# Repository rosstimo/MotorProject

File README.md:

# MotorProject
Super Fantastic Motor Project

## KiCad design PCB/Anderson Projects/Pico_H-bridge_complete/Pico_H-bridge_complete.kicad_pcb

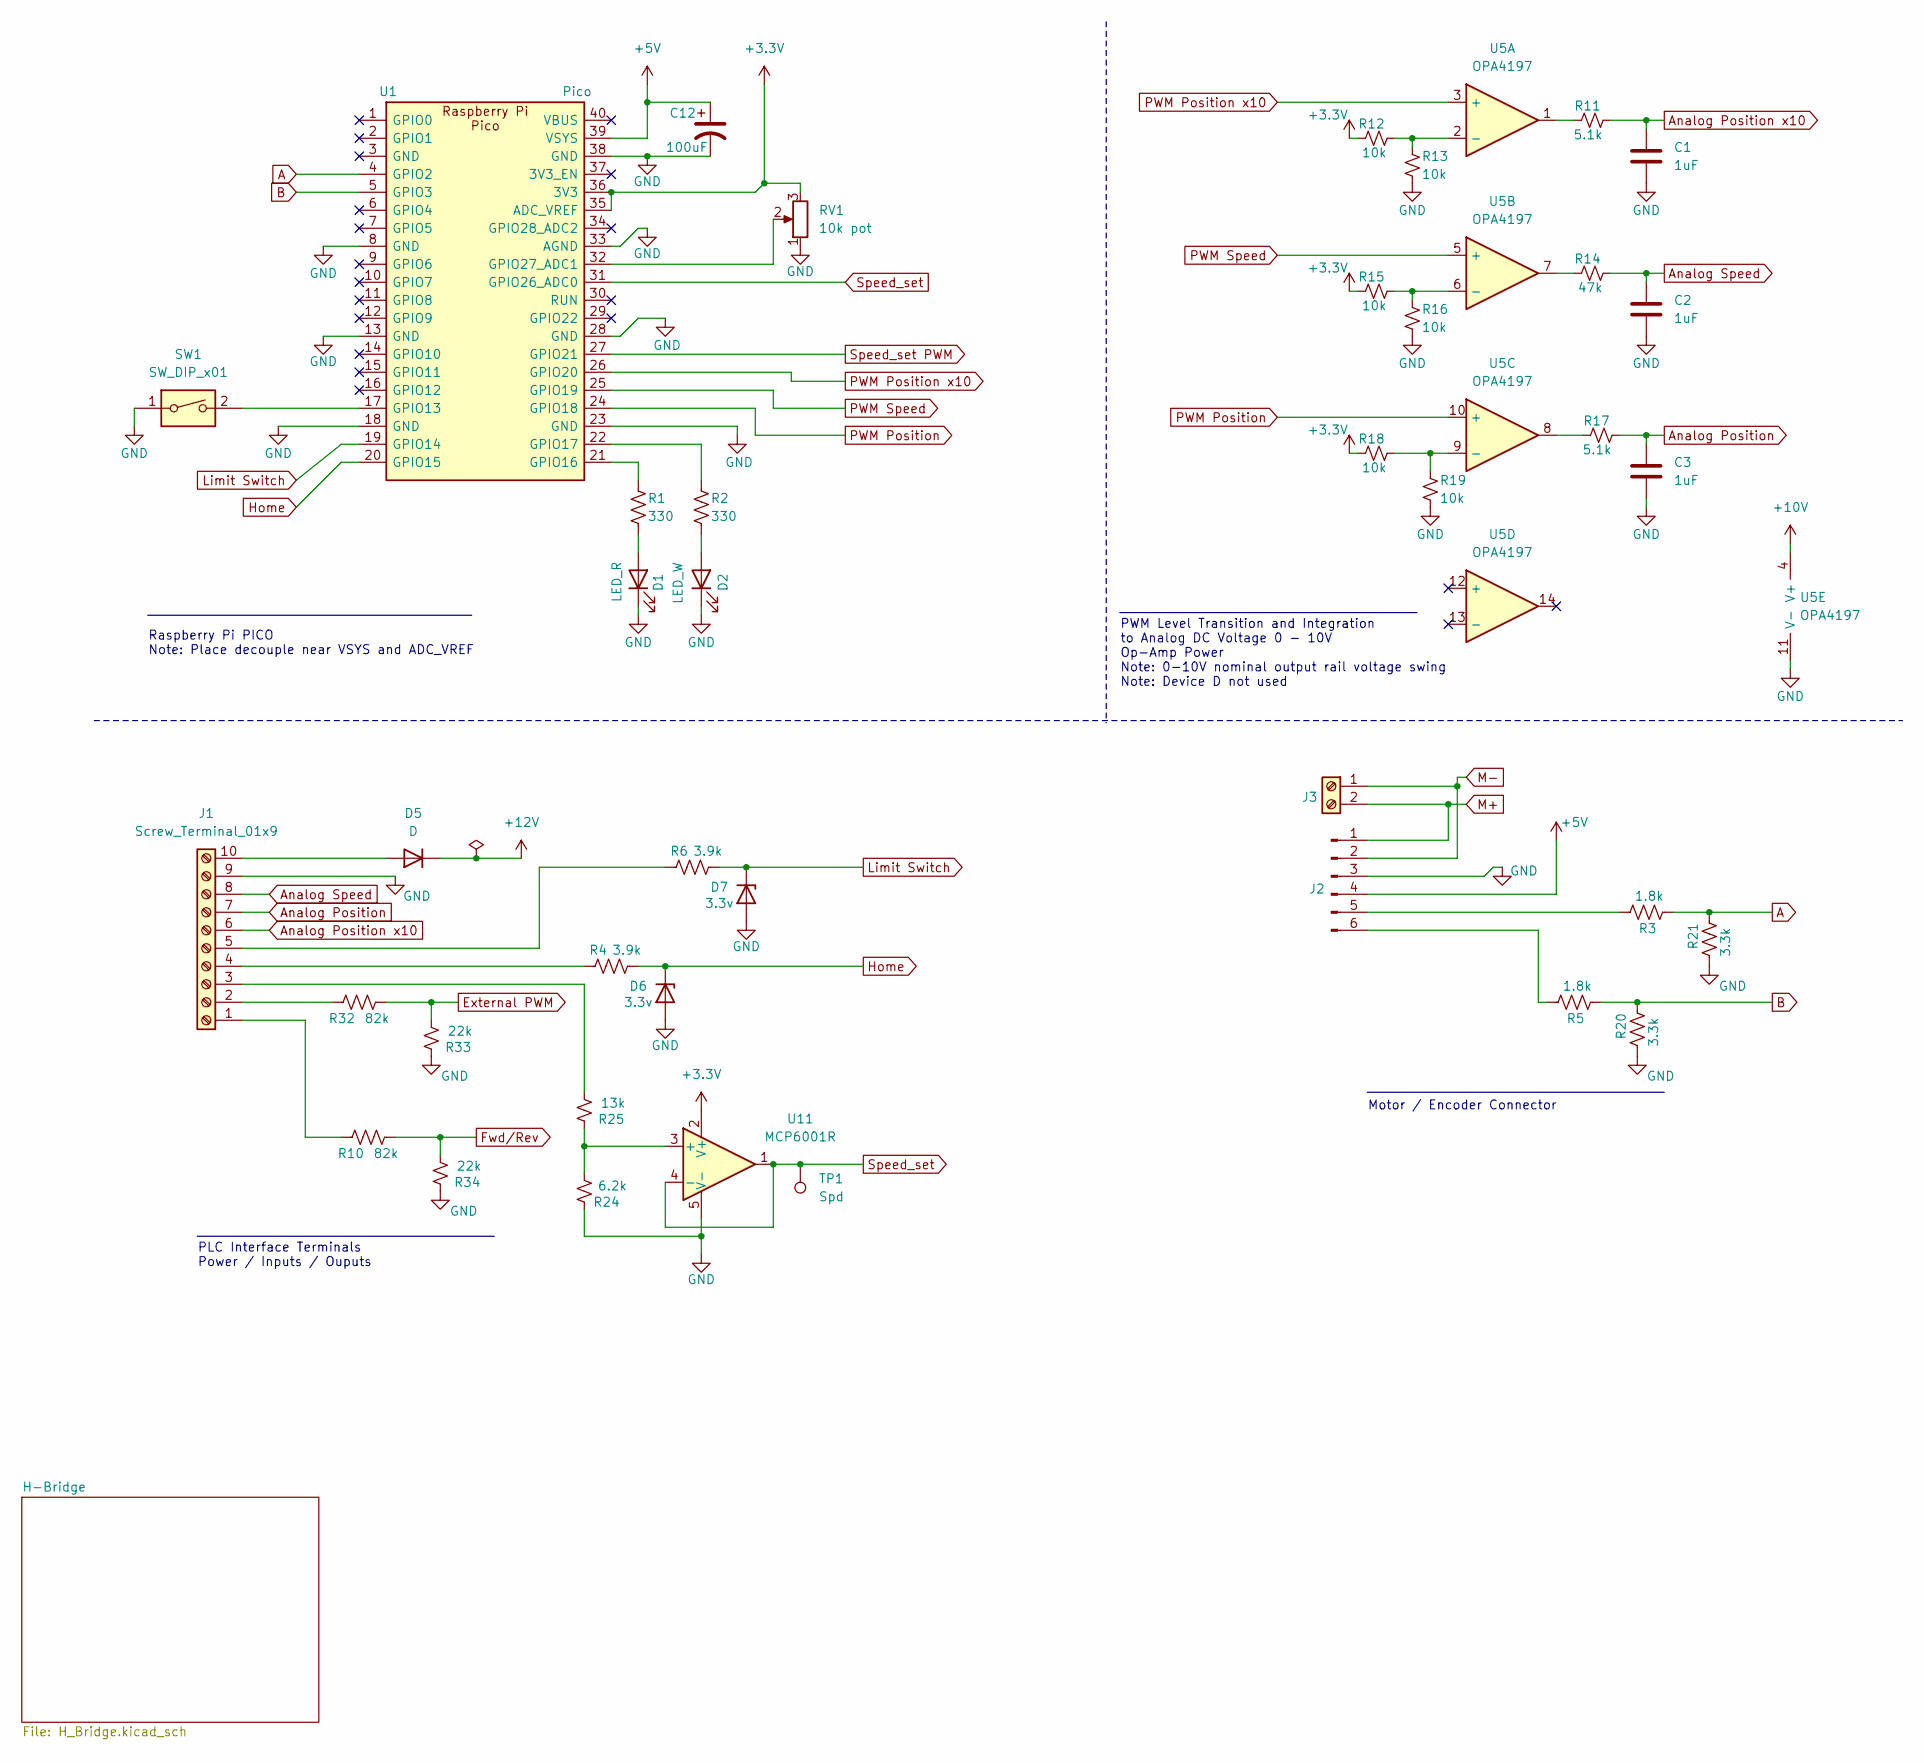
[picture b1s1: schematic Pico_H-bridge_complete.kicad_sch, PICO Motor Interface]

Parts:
C1, C2, C3: 1uF; C_1206_3216Metric; LCSC C2167419
C12: 100uF; C_1210_3225Metric; LCSC C23742
D1: LED_R; LED_0805_2012Metric; LCSC C84256
D2: LED_W; LED_0805_2012Metric; LCSC C34499
D5: D; D_SMA; LCSC C8678
D6, D7: 3.3v; D_SOD-323; LCSC C19077437
J1: Screw_Terminal_01x9; TerminalBlock_Phoenix_PT-1,5-10-5.0-H_1x10_P5.00mm_Horizont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
J2: Motor Connector; JST_XH_B6B-XH-A_1x06_P2.50mm_Vertical
J3: Screw_Terminal_01x02; TerminalBlock_Phoenix_MKDS-1,5-2_1x02_P5.00mm_Horizontal
R1, R2: 330; R_0805_2012Metric_Pad1.20x1.40mm_HandSolder; LCSC C17630
R3, R5: 1.8k; R_0805_2012Metric_Pad1.20x1.40mm_HandSolder; LCSC C17398
R4, R6: 3.9k; R_0805_2012Metric_Pad1.20x1.40mm_HandSolder; LCSC C17614
R10, R32: 82k; R_0805_2012Metric_Pad1.20x1.40mm_HandSolder; LCSC C17840
R11, R17: 5.1k; R_0805_2012Metric_Pad1.20x1.40mm_HandSolder; LCSC C27834
R12, R13, R15, R16, R18, R19: 10k; R_0805_2012Metric_Pad1.20x1.40mm_HandSolder; LCSC C17414
R14: 47k; R_0805_2012Metric_Pad1.20x1.40mm_HandSolder; LCSC C17713
R20, R21: 3.3k; R_0805_2012Metric_Pad1.20x1.40mm_HandSolder; LCSC C26010
R24: 6.2k; R_0805_2012Metric_Pad1.20x1.40mm_HandSolder; LCSC C17767
R25: 13k; R_0805_2012Metric_Pad1.20x1.40mm_HandSolder; LCSC C17455
R33, R34: 22k; R_0805_2012Metric_Pad1.20x1.40mm_HandSolder; LCSC C17560
RV1: 10k pot; Potentiometer_Bourns_3314J_Vertical; LCSC C36376
SW1: SW_DIP_x01; DIP_1x01_3.5_6.2mm; LCSC C600988
TP1: Spd; TestPoint_Plated_Hole_D2.0mm
U1: Pico; RaspberryPi_Pico
U5: OPA4197; SO-14_5.4_P1.27; LCSC C2058532
U11: MCP6001R; SOT-23-5; LCSC C154973

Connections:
+3.3V: R12.1, R15.1, R18.1, RV1.3, U1.35 (ADC_VREF), U1.36 (3V3), U11.2 (V+)
+5V: C12.1, J2.4, U1.39 (VSYS); also elsewhere on the board
+10V: U5.4 (V+); also elsewhere on the board
+12V: D5.1 (K); also elsewhere on the board
A: R3.2, R21.1, U1.4 (GPIO2)
Analog Position: C3.1, J1.7, R17.2
Analog Position x10: C1.1, J1.6, R11.2
Analog Speed: C2.1, J1.8, R14.2
B: R5.2, R20.1, U1.5 (GPIO3)
External PWM: R32.2, R33.2; also elsewhere on the board
Fwd/Rev: R10.2, R34.2; also elsewhere on the board
GND: C1.2, C2.2, C3.2, C12.2, D1.1 (K), D2.1 (K), D6.2 (A), D7.2 (A), J1.9, J2.3, R13.2, R16.2, R19.2, R20.2, R21.2, R24.1, R33.1, R34.1, RV1.1, SW1.1, U1.8 (GND), U1.13 (GND), U1.18 (GND), U1.23 (GND), U1.28 (GND), U1.33 (AGND), U1.38 (GND), U5.11 (V-), U11.5 (V-); also elsewhere on the board
Home: D6.1 (K), R4.2, U1.20 (GPIO15)
Limit Switch: D7.1 (K), R6.2, U1.19 (GPIO14)
M+: J2.1, J3.2; also elsewhere on the board
M-: J2.2, J3.1; also elsewhere on the board
unnamed: D1.2 (A), R1.2
unnamed: D2.2 (A), R2.2
unnamed: D5.2 (A), J1.10
unnamed: J1.1, R10.1
unnamed: J1.2, R32.1
unnamed: J1.3, R25.2
unnamed: J1.4, R4.1
unnamed: J1.5, R6.1
unnamed: J2.5, R3.1
unnamed: J2.6, R5.1
unnamed: R11.1, U5.1
unnamed: R14.1, U5.7
unnamed: R17.1, U5.8
unnamed: SW1.2, U1.17 (GPIO13)
unnamed: R1.1, U1.21 (GPIO16)
unnamed: R2.1, U1.22 (GPIO17)
unnamed: RV1.2, U1.32 (GPIO27_ADC1)
unnamed: R12.2, R13.1, U5.2 (-)
unnamed: R15.2, R16.1, U5.6 (-)
unnamed: R18.2, R19.1, U5.9 (-)
unnamed: R24.2, R25.1, U11.3 (+)
PWM Position: U1.24 (GPIO18), U5.10 (+)
PWM Position x10: U1.26 (GPIO20), U5.3 (+)
PWM Speed: U1.25 (GPIO19), U5.5 (+)
Speed_set: TP1.1, U1.31 (GPIO26_ADC0), U11.1, U11.4 (-)
Speed_set PWM: U1.27 (GPIO21); also elsewhere on the board

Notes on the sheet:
PWM Level Transition and Integration to Analog DC Voltage 0 - 10V Op-Amp Power Note: 0-10V nominal output rail voltage swing Note: Device D not used
PLC Interface Terminals Power / Inputs / Ouputs
Motor / Encoder Connector
Raspberry Pi PICO Note: Place decouple near VSYS and ADC_VREF

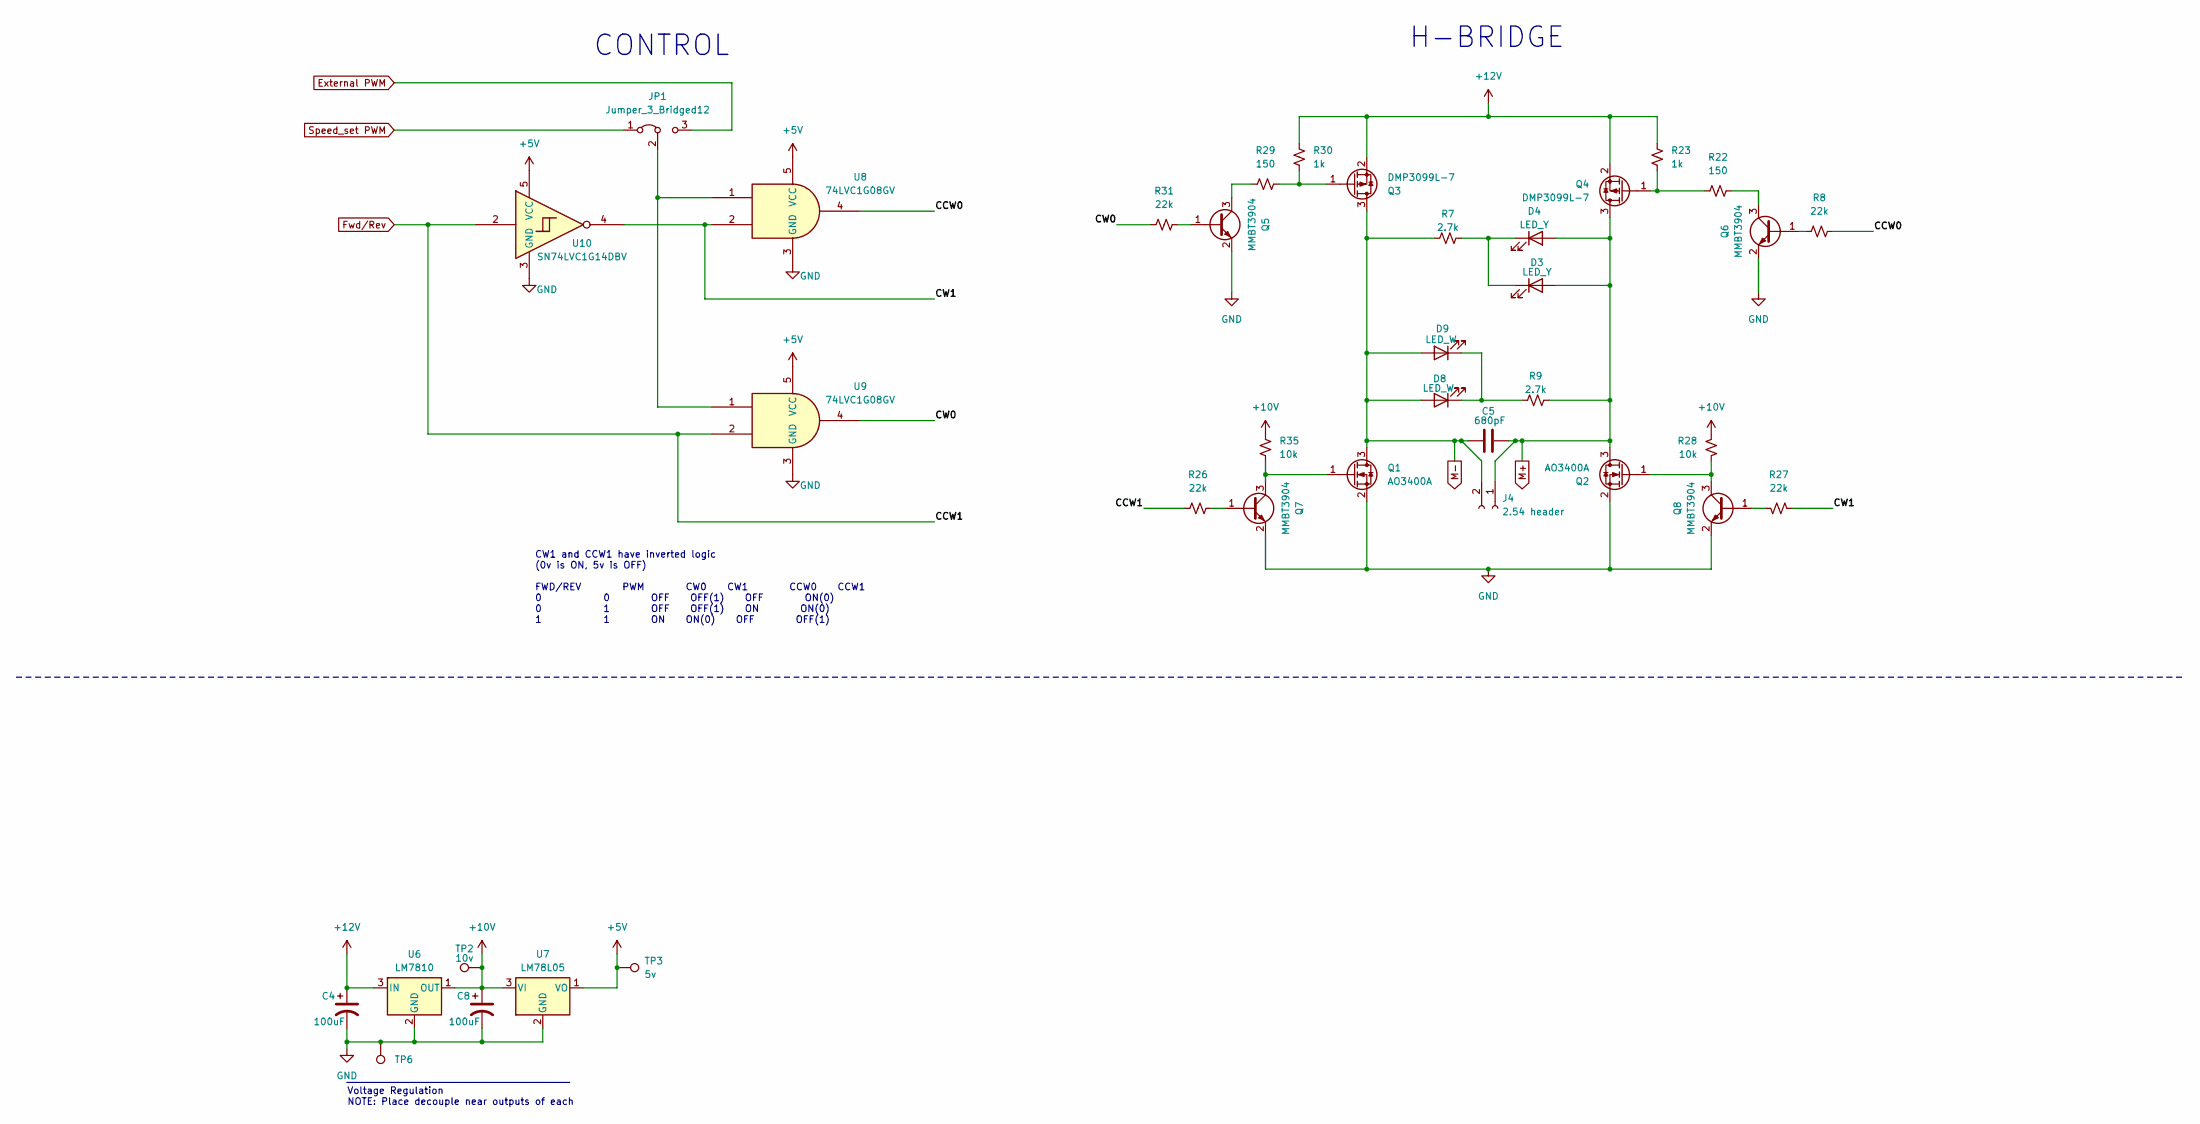
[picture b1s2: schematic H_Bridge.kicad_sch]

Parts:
C4, C8: 100uF; C_1210_3225Metric; LCSC C23742
C5: 680pF; C_0603_1608Metric; LCSC C1630
D3, D4: LED_Y; LED_0603_1608Metric; LCSC C2286
D8, D9: LED_W; LED_0603_1608Metric; LCSC C2290
J4: 2.54 header; PinHeader_1x02_P2.54mm_Vertical
JP1: Jumper_3_Bridged12; PinHeader_1x03_P2.54mm_Vertical
Q1, Q2: AO3400A; SOT-23; LCSC C20917
Q3, Q4: DMP3099L-7; SOT-23; LCSC C155244
Q5, Q6, Q7, Q8: MMBT3904; SOT-23; LCSC C20526
R7, R9: 2.7k; R_0805_2012Metric_Pad1.20x1.40mm_HandSolder; LCSC C17530
R8, R26, R27, R31: 22k; R_0805_2012Metric_Pad1.20x1.40mm_HandSolder; LCSC C17560
R22, R29: 150; R_0805_2012Metric_Pad1.20x1.40mm_HandSolder; LCSC C17471
R23, R30: 1k; R_0805_2012Metric_Pad1.20x1.40mm_HandSolder; LCSC C17513
R28, R35: 10k; R_0805_2012Metric_Pad1.20x1.40mm_HandSolder; LCSC C17414
TP2: 10v; TestPoint_Plated_Hole_D2.0mm
TP3: 5v; TestPoint_Plated_Hole_D2.0mm
TP6: GND; TestPoint_Loop_D2.60mm_Drill1.4mm_Beaded
U6: LM7810; SOT-89-3; LCSC C122848
U7: LM78L05; SOT-89-3; LCSC C347258
U8, U9: 74LVC1G08GV; SOT-23-5; LCSC C19829591
U10: SN74LVC1G14DBV; SOT-23-5; LCSC C7835

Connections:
+5V: TP3.1, U7.1 (VO), U8.5 (VCC), U9.5 (VCC), U10.5 (VCC); also elsewhere on the board
+10V: C8.1, R28.1, R35.1, TP2.1, U6.1 (OUT), U7.3 (VI); also elsewhere on the board
+12V: C4.1, Q3.2 (S), Q4.2 (S), R23.2, R30.2, U6.3 (IN); also elsewhere on the board
/H-Bridge/CCW0: R8.2, U8.4
/H-Bridge/CW0: R31.1, U9.4
/H-Bridge/CW1: R27.1, U8.2, U10.4
External PWM: JP1.3 (B); also elsewhere on the board
Fwd/Rev: R26.1, U9.2, U10.2; also elsewhere on the board
GND: C4.2, C8.2, Q1.2 (S), Q2.2 (S), Q5.2 (E), Q6.2 (E), Q7.2 (E), Q8.2 (E), TP6.1, U6.2 (GND), U7.2 (GND), U8.3 (GND), U9.3 (GND), U10.3 (GND); also elsewhere on the board
M+: C5.2, D3.2 (A), D4.2 (A), J4.1, Q2.3 (D), Q4.3 (D), R9.1; also elsewhere on the board
M-: C5.1, D8.2 (A), D9.2 (A), J4.2, Q1.3 (D), Q3.3 (D), R7.2; also elsewhere on the board
unnamed: D3.1 (K), D4.1 (K), R7.1
unnamed: D8.1 (K), D9.1 (K), R9.2
unnamed: JP1.2 (C), U8.1, U9.1
unnamed: Q1.1 (G), Q7.3 (C), R35.2
unnamed: Q2.1 (G), Q8.3 (C), R28.2
unnamed: Q3.1 (G), R29.2, R30.1
unnamed: Q4.1 (G), R22.1, R23.1
unnamed: Q5.1 (B), R31.2
unnamed: Q5.3 (C), R29.1
unnamed: Q6.1 (B), R8.1
unnamed: Q6.3 (C), R22.2
unnamed: Q7.1 (B), R26.2
unnamed: Q8.1 (B), R27.2
Speed_set PWM: JP1.1 (A); also elsewhere on the board

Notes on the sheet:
Voltage Regulation NOTE: Place decouple near outputs of each
CONTROL
CW1 and CCW1 have inverted logic (0v is ON, 5v is OFF) FWD/REV PWM CW0 CW1 CCW0 CCW1 0 0 OFF OFF(1) OFF ON(0) 0 1 OFF OFF(1) ON ON(0) 1 1 ON ON(0) OFF OFF(1)
H-BRIDGE

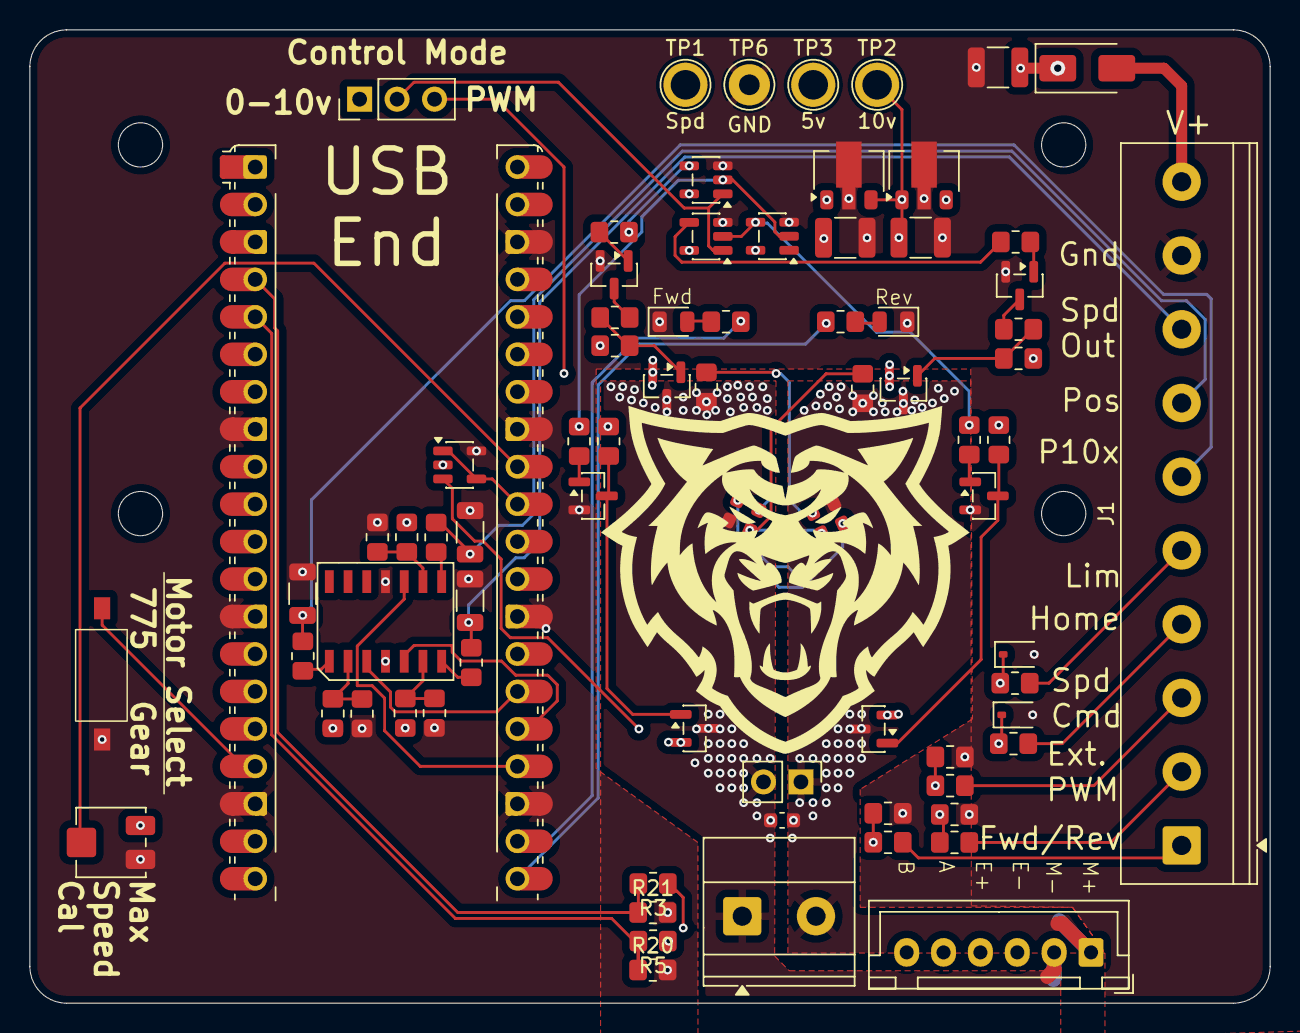
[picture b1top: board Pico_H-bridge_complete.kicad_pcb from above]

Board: 4 copper layers, 84.1 x 66.0 mm, 79 parts (0 on the bottom side), 58 nets.

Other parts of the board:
logo1: LOGO; Bengal_25_25(negative)

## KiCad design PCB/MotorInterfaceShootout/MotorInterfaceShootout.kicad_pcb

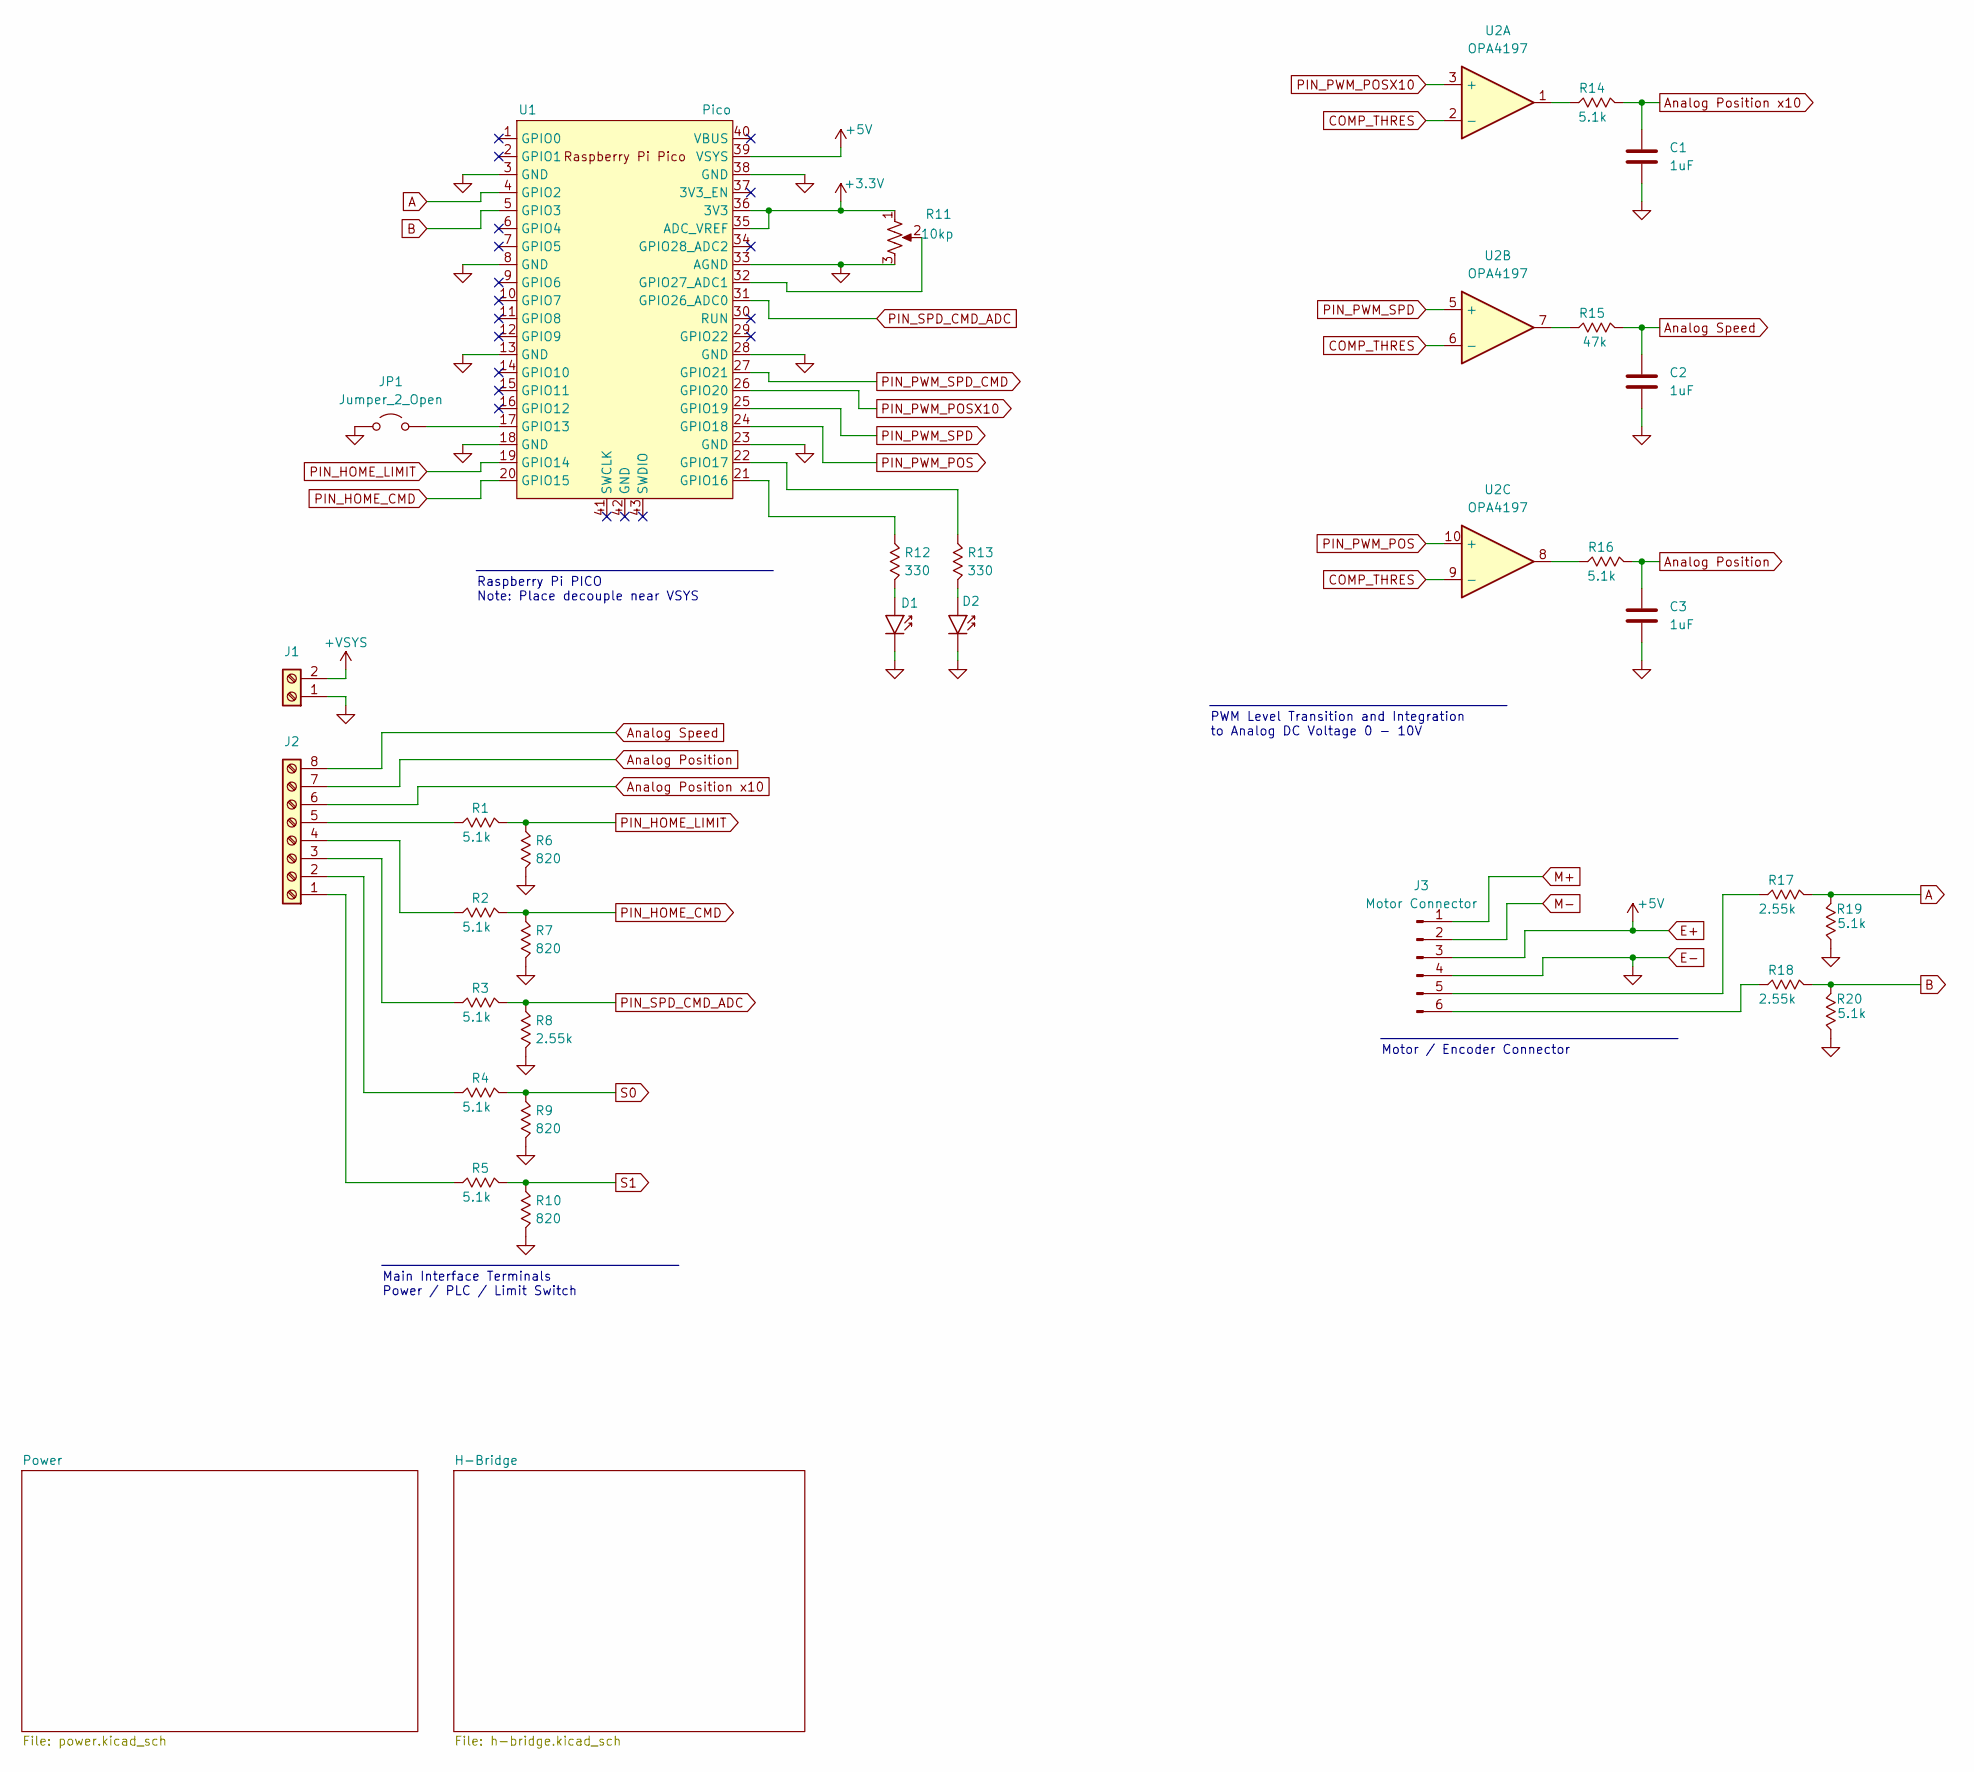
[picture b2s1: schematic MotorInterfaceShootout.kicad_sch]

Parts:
C1, C2, C3: 1uF; C_Rect_L7.3mm_W4.5_H9.5mm_P5.0mmx
D1: Red; LED_0805_2012Metric_Pad1.15x1.40mm_HandSolder
D2: Green; LED_0805_2012Metric_Pad1.15x1.40mm_HandSolder
J1: Screw_Terminal_01x02; TerminalBlock_WAGO_236-102_1x02_P5.00mm_45Degree
J2: Screw_Terminal_01x08; TerminalBlock_WAGO_236-108_1x08_P5.00mm_45Degree
J3: Motor Connector; JST_XH_B6B-XH-A_1x06_P2.50mm_Vertical
JP1: Jumper_2_Open; PinHeader_1x02_P2.54mm_Vertical
R1, R2, R3, R4, R5, R14, R16, R19, R20: 5.1k; R_0805_2012Metric
R6, R7, R9, R10: 820; R_0805_2012Metric
R8, R17, R18: 2.55k; R_0805_2012Metric
R11: 10kp; SOT_10KLFTR_BIT
R12, R13: 330; R_0805_2012Metric
R15: 47k; R_0805_2012Metric
U1: Pico; RPi_Pico_SMD_TH
U2: OPA4197; D14_TEX

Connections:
+3.3V: R11.1, U1.35 (ADC_VREF), U1.36 (3V3)
+VSYS: J1.2; also elsewhere on the board
A: R17.2, R19.2, U1.4 (GPIO2)
Analog Position: C3.1, J2.7, R16.2
Analog Position x10: C1.1, J2.6, R14.2
Analog Speed: C2.1, J2.8, R15.2
B: R18.2, R20.2, U1.5 (GPIO3)
COMP_THRES: U2.2 (-), U2.6 (-), U2.9 (-); also elsewhere on the board
E+: J3.3, U1.39 (VSYS); also elsewhere on the board
E-: C1.2, C2.2, C3.2, D1.1 (K), D2.1 (K), J1.1, J3.4, JP1.1 (A), R6.2, R7.2, R8.2, R9.2, R10.2, R11.3, R19.1, R20.1, U1.3 (GND), U1.8 (GND), U1.13 (GND), U1.18 (GND), U1.23 (GND), U1.28 (GND), U1.33 (AGND), U1.38 (GND); also elsewhere on the board
M+: J3.1; also elsewhere on the board
M-: J3.2; also elsewhere on the board
unnamed: D1.2 (A), R12.2
unnamed: D2.2 (A), R13.2
unnamed: J2.1, R5.1
unnamed: J2.2, R4.1
unnamed: J2.3, R3.1
unnamed: J2.4, R2.1
unnamed: J2.5, R1.1
unnamed: J3.5, R17.1
unnamed: J3.6, R18.1
unnamed: JP1.2 (B), U1.17 (GPIO13)
unnamed: R14.1, U2.1
unnamed: R15.1, U2.7
unnamed: R16.1, U2.8
unnamed: R12.1, U1.21 (GPIO16)
unnamed: R13.1, U1.22 (GPIO17)
unnamed: R11.2, U1.32 (GPIO27_ADC1)
PIN_HOME_CMD: R2.2, R7.1, U1.20 (GPIO15)
PIN_HOME_LIMIT: R1.2, R6.1, U1.19 (GPIO14)
PIN_PWM_POS: U1.24 (GPIO18), U2.10 (+)
PIN_PWM_POSX10: U1.26 (GPIO20), U2.3 (+)
PIN_PWM_SPD: U1.25 (GPIO19), U2.5 (+)
PIN_PWM_SPD_CMD: U1.27 (GPIO21); also elsewhere on the board
PIN_SPD_CMD_ADC: R3.2, R8.1, U1.31 (GPIO26_ADC0)
S0: R4.2, R9.1; also elsewhere on the board
S1: R5.2, R10.1; also elsewhere on the board

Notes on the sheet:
Motor / Encoder Connector
Raspberry Pi PICO Note: Place decouple near VSYS
PWM Level Transition and Integration to Analog DC Voltage 0 - 10V
Main Interface Terminals Power / PLC / Limit Switch

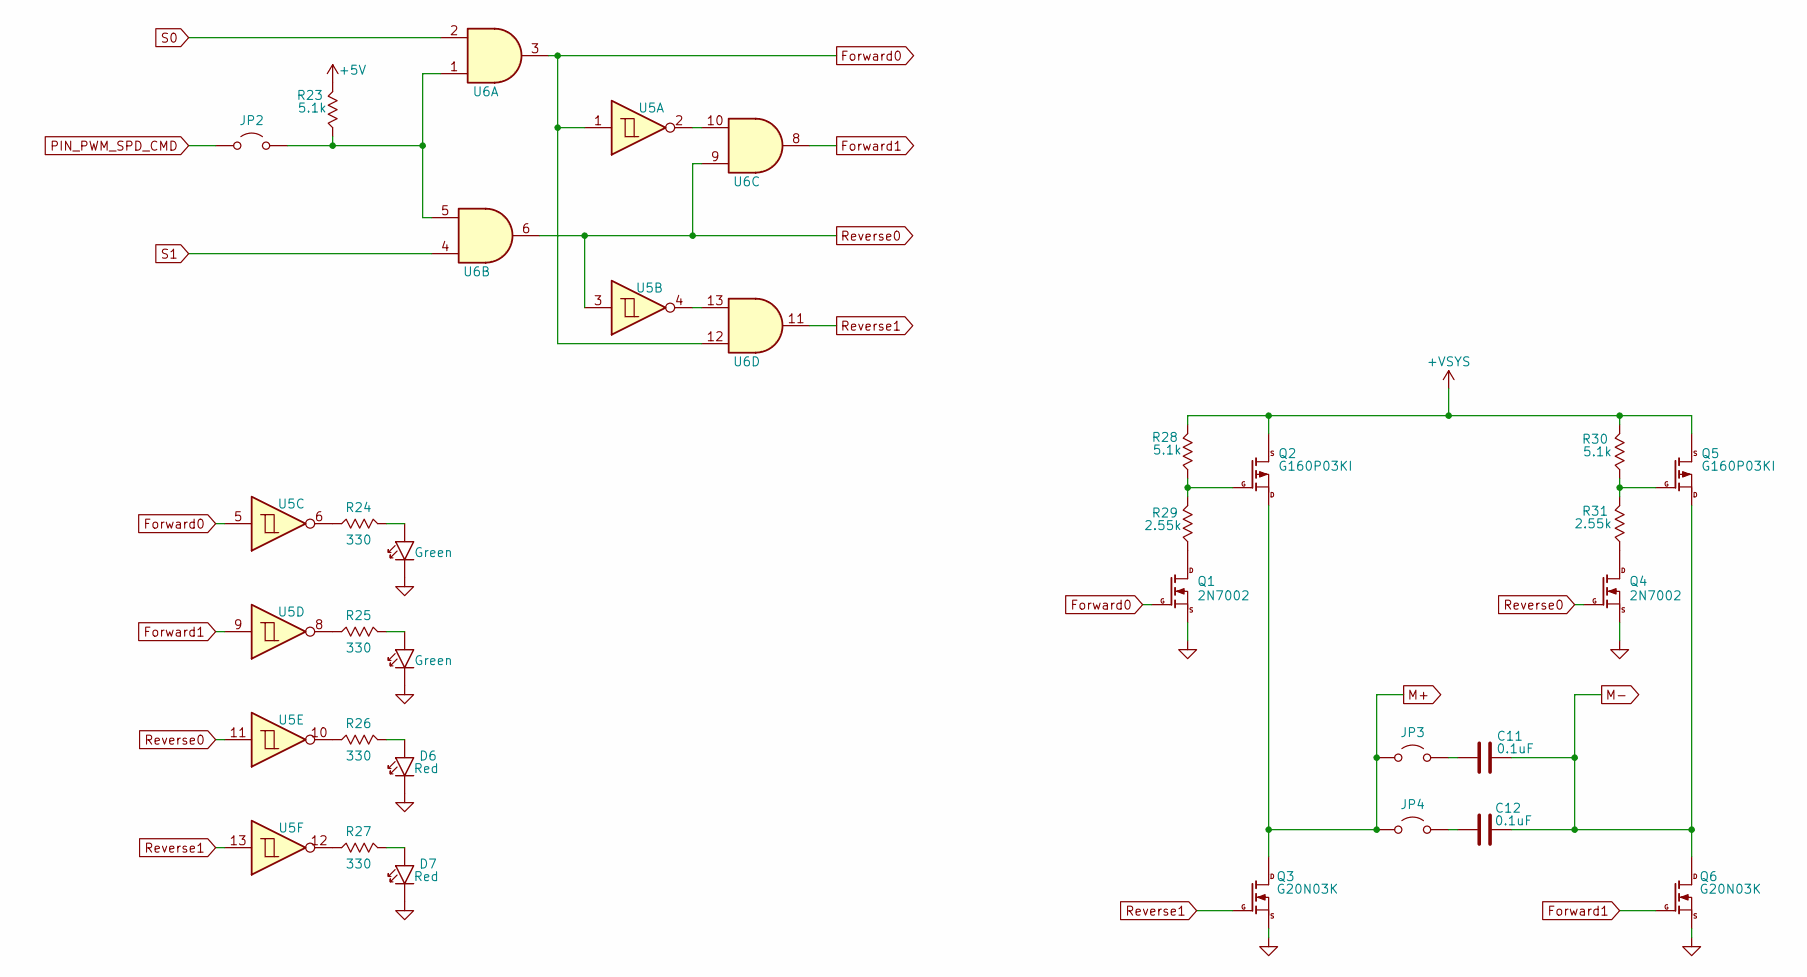
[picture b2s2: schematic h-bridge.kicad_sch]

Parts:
C11, C12: 0.1uF; C_0805_2012Metric
D4, D5: Green; LED_0805_2012Metric_Pad1.15x1.40mm_HandSolder
D6, D7: Red; LED_0805_2012Metric_Pad1.15x1.40mm_HandSolder
JP2, JP3, JP4: Jumper_2_Open; PinHeader_1x02_P2.54mm_Vertical
Q1, Q4: 2N7002; SOT-23
Q2, Q5: G160P03KI; TO-252-2
Q3, Q6: G20N03K; TO-252-2
R23, R28, R30: 5.1k; R_0805_2012Metric
R24, R25, R26, R27: 330; R_0805_2012Metric
R29, R31: 2.55k; R_0805_2012Metric
U5: 74LS14; SOIC-14_3.9x8.7mm_P1.27mm-D14-L
U6: 74LS08; SOIC-14_3.9x8.7mm_P1.27mm-D14-L

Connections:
+VSYS: Q2.3 (S), Q5.3 (S), R28.2, R30.2; also elsewhere on the board
E+: R23.2; also elsewhere on the board
E-: D4.1 (K), D5.1 (K), D6.1 (K), D7.1 (K), Q1.2 (S), Q3.3 (S), Q4.2 (S), Q6.3 (S); also elsewhere on the board
Forward0: Q1.1 (G), U5.1, U5.5, U6.3, U6.12
Forward1: Q6.1 (G), U5.9, U6.8
M+: JP3.1 (A), JP4.1 (A), Q2.2 (D), Q3.2 (D); also elsewhere on the board
M-: C11.2, C12.2, Q5.2 (D), Q6.2 (D); also elsewhere on the board
unnamed: D4.2 (A), R24.2
unnamed: D5.2 (A), R25.2
unnamed: D6.2 (A), R26.2
unnamed: D7.2 (A), R27.2
unnamed: JP2.2 (B), R23.1, U6.1, U6.5
unnamed: C11.1, JP3.2 (B)
unnamed: C12.1, JP4.2 (B)
unnamed: Q1.3 (D), R29.1
unnamed: Q2.1 (G), R28.1, R29.2
unnamed: Q4.3 (D), R31.1
unnamed: Q5.1 (G), R30.1, R31.2
unnamed: R24.1, U5.6
unnamed: R25.1, U5.8
unnamed: R26.1, U5.10
unnamed: R27.1, U5.12
unnamed: U5.2, U6.10
unnamed: U5.4, U6.13
PIN_PWM_SPD_CMD: JP2.1 (A); also elsewhere on the board
Reverse0: Q4.1 (G), U5.3, U5.11, U6.6, U6.9
Reverse1: Q3.1 (G), U5.13, U6.11
S0: U6.2; also elsewhere on the board
S1: U6.4; also elsewhere on the board

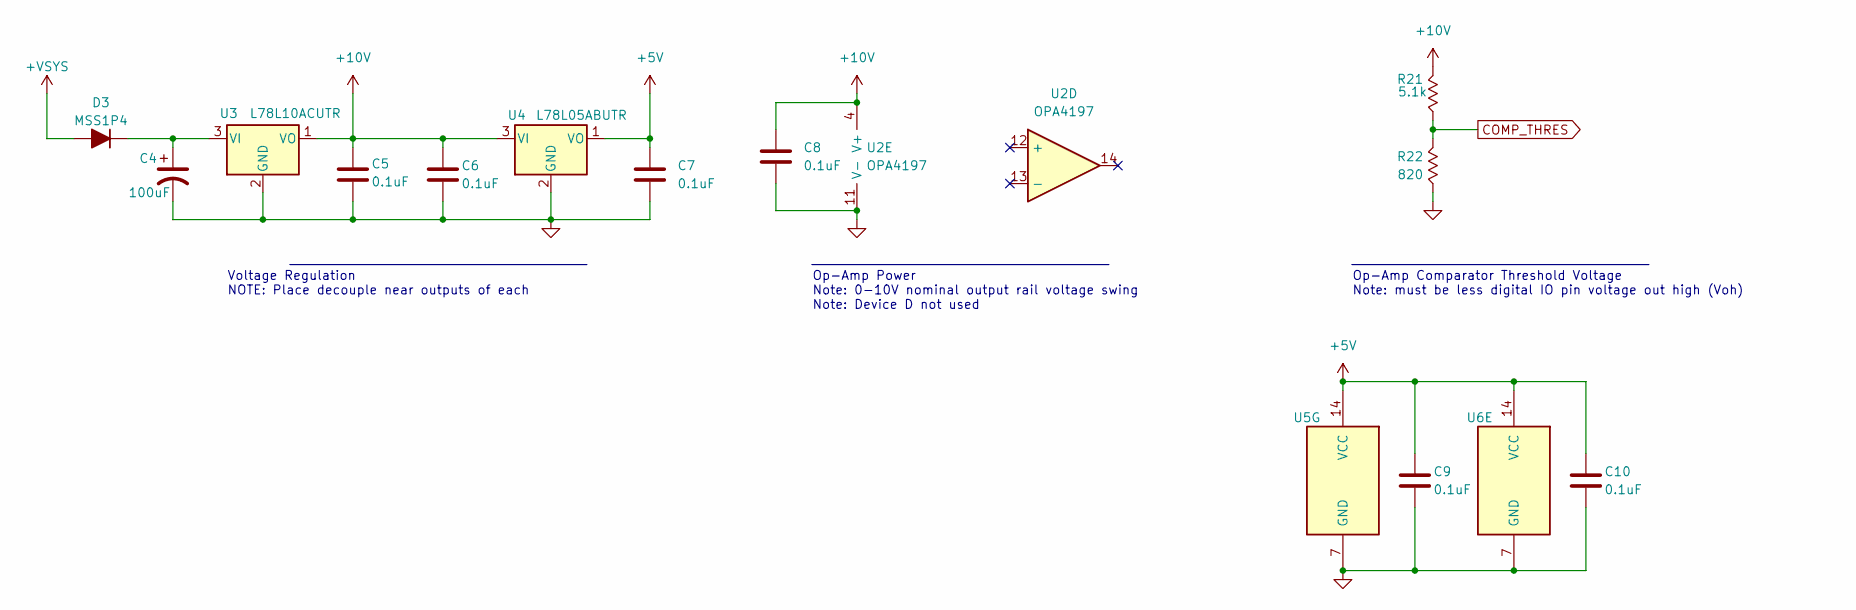
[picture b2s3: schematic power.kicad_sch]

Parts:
C4: 100uF; CP_Elec_6.3x7.7
C5, C6, C7, C8, C9, C10: 0.1uF; C_0805_2012Metric
D3: MSS1P4; D_MicroSMP_AK
R21: 5.1k; R_0805_2012Metric
R22: 820; R_0805_2012Metric
U2: OPA4197; D14_TEX
U3: L78L10ACUTR; SOT-89-3
U4: L78L05ABUTR; SOT-89-3
U5: 74LS14; SOIC-14_3.9x8.7mm_P1.27mm-D14-L
U6: 74LS08; SOIC-14_3.9x8.7mm_P1.27mm-D14-L

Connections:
+10V: C5.1, C6.1, C8.1, R21.2, U2.4 (V+), U3.1 (VO), U4.3 (VI)
+VSYS: D3.2 (A); also elsewhere on the board
COMP_THRES: R21.1, R22.1; also elsewhere on the board
E+: C7.1, C9.1, C10.1, U4.1 (VO), U5.14 (VCC), U6.14 (VCC); also elsewhere on the board
E-: C4.2, C5.2, C6.2, C7.2, C8.2, C9.2, C10.2, R22.2, U2.11 (V-), U3.2 (GND), U4.2 (GND), U5.7 (GND), U6.7 (GND); also elsewhere on the board
unnamed: C4.1, D3.1 (K), U3.3 (VI)

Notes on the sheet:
Voltage Regulation NOTE: Place decouple near outputs of each
Op-Amp Power Note: 0-10V nominal output rail voltage swing Note: Device D not used
Op-Amp Comparator Threshold Voltage Note: must be less digital IO pin voltage out high (Voh)

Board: 4 copper layers, 69 parts (23 on the bottom side), 60 nets, no tracks yet.

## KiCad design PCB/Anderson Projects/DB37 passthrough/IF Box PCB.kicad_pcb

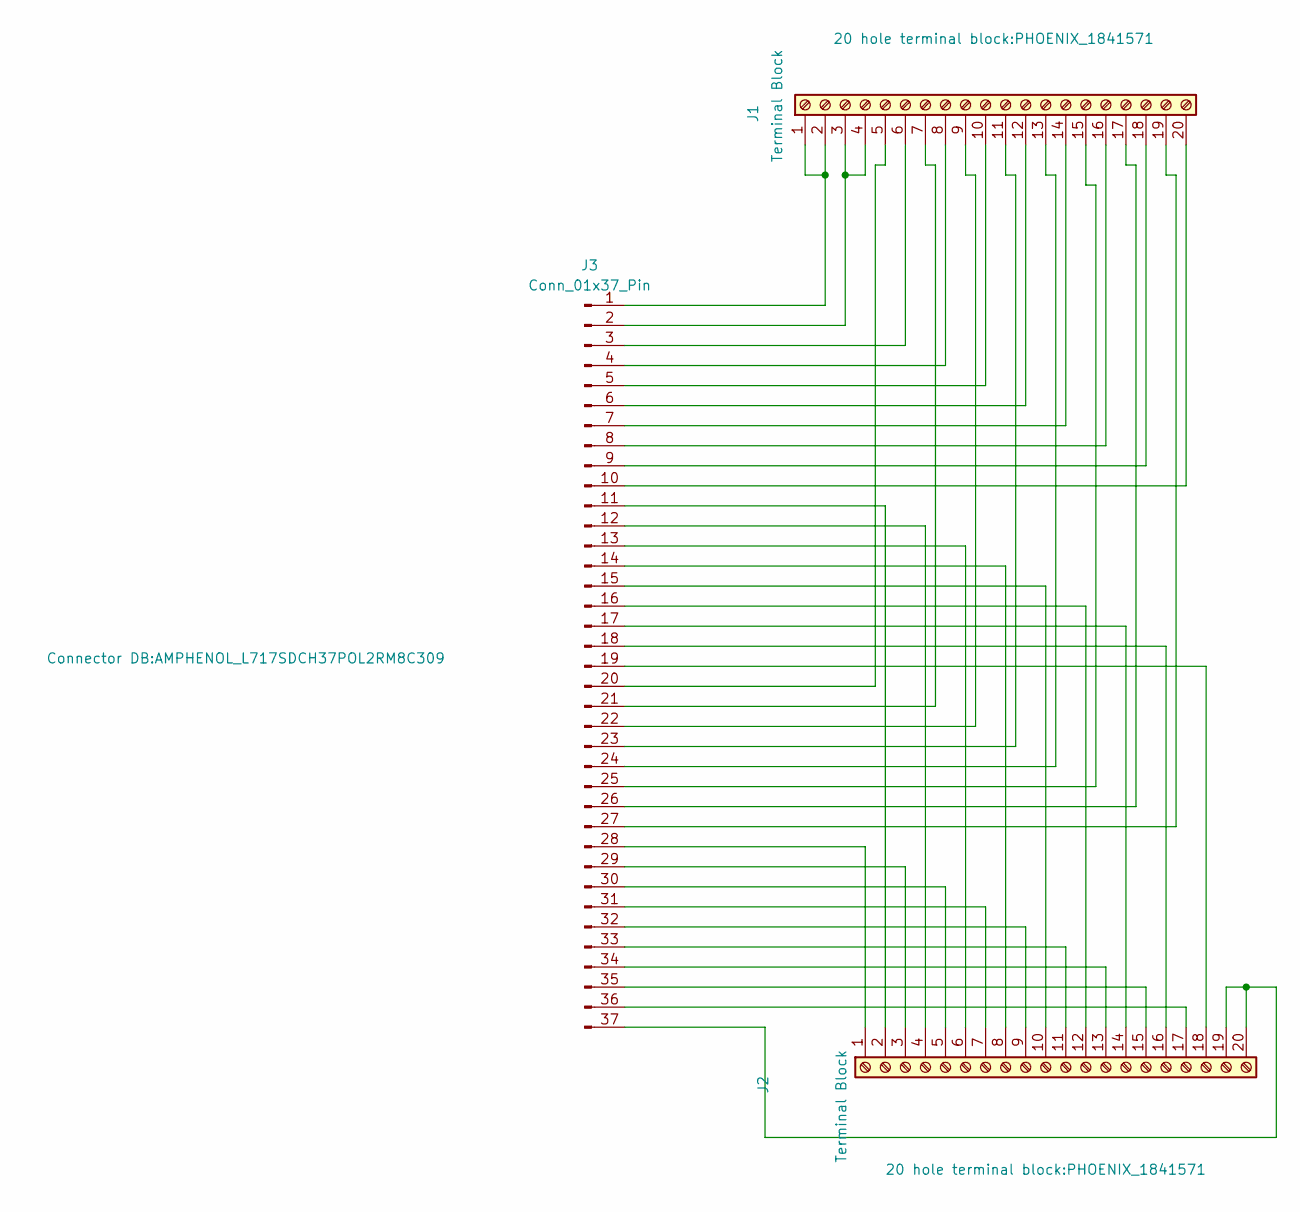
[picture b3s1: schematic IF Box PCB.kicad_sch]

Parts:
J1, J2: Terminal Block; PHOENIX_1841571
J3: Conn_01x37_Pin; AMPHENOL_L717SDCH37POL2RM8C309

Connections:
unnamed: J1.1, J1.2, J3.1
unnamed: J1.3, J1.4, J3.2
unnamed: J1.5, J3.20
unnamed: J1.6, J3.3
unnamed: J1.7, J3.21
unnamed: J1.8, J3.4
unnamed: J1.9, J3.22
unnamed: J1.10, J3.5
unnamed: J1.11, J3.23
unnamed: J1.12, J3.6
unnamed: J1.13, J3.24
unnamed: J1.14, J3.7
unnamed: J1.15, J3.25
unnamed: J1.16, J3.8
unnamed: J1.17, J3.26
unnamed: J1.18, J3.9
unnamed: J1.19, J3.27
unnamed: J1.20, J3.10
unnamed: J2.1, J3.28
unnamed: J2.2, J3.11
unnamed: J2.3, J3.29
unnamed: J2.4, J3.12
unnamed: J2.5, J3.30
unnamed: J2.6, J3.13
unnamed: J2.7, J3.31
unnamed: J2.8, J3.14
unnamed: J2.9, J3.32
unnamed: J2.10, J3.15
unnamed: J2.11, J3.33
unnamed: J2.12, J3.16
unnamed: J2.13, J3.34
unnamed: J2.14, J3.17
unnamed: J2.15, J3.35
unnamed: J2.16, J3.18
unnamed: J2.17, J3.36
unnamed: J2.18, J3.19
unnamed: J2.19, J2.20, J3.37
